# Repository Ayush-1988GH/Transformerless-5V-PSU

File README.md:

# Transformerless-5V-PSU
A compact transformerless AC-to-DC power supply designed using a capacitive dropper, bridge rectifier, zener protection, and LM7805 voltage regulator.  This project was built to understand low-power offline power supply design and mains-side electronics.

## Features
- 230V AC input
- Capacitive current limiting
- Full-wave bridge rectification
- Ripple filtering
- Zener overvoltage protection
- Regulated 5V DC output
- LED power indication

| Component    | Purpose            |
| ------------ | ------------------ |
| X2 Capacitor | Current limiting   |
| 1N4007       | Rectification      |
| LM7805       | 5V regulation      |
| Zener Diode  | Voltage protection |

⚠ WARNING:
This circuit is non-isolated from AC mains.
Do NOT touch while powered.
Do NOT connect directly to a computer USB port.
Only for educational and experimental purposes.

## What I Learned
- Basics of capacitive dropper supplies
- AC to DC rectification
- PCB design considerations for mains voltage
- Filtering and voltage regulation
- Safety considerations in non-isolated supplies

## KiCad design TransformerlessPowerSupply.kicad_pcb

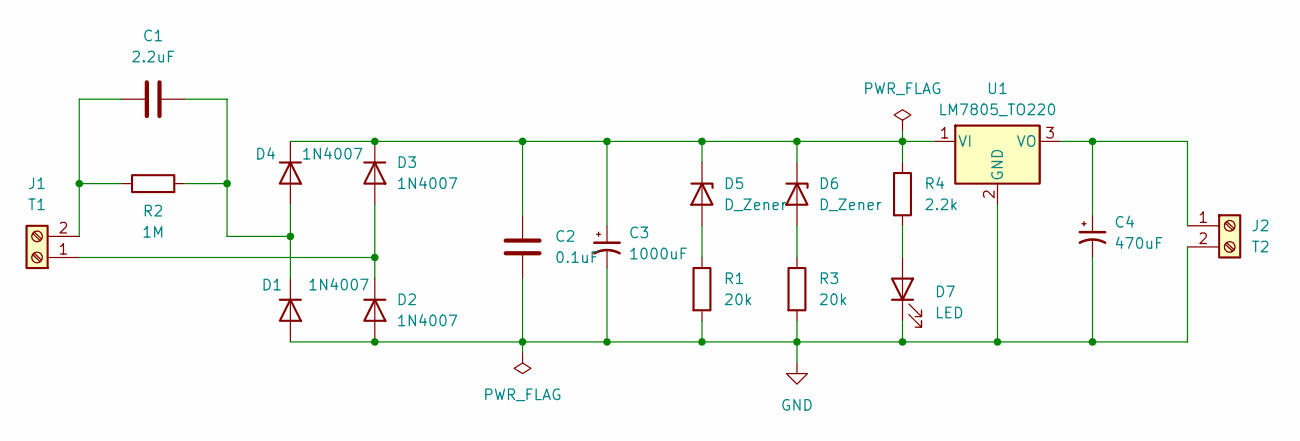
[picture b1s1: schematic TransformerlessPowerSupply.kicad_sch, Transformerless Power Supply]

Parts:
C1: 2.2uF; C_Rect_L18.0mm_W6.0mm_P15.00mm_FKS3_FKP3
C2: 0.1uF; C_Disc_D10.0mm_W2.5mm_P5.00mm
C3: 1000uF; CP_Axial_L10.0mm_D4.5mm_P15.00mm_Horizontal
C4: 470uF; CP_Elec_3x5.4
D1, D2, D3, D4: 1N4007; D_DO-41_SOD81_P10.16mm_Horizontal
D5, D6: D_Zener; D_DO-34_SOD68_P7.62mm_Horizontal
D7: LED; LED_1206_3216Metric
J1: T1; TerminalBlock_Phoenix_PT-1,5-2-5.0-H_1x02_P5.00mm_Horizontal
J2: T2; TerminalBlock_Phoenix_MKDS-1-2-3.81_1x02_P3.81mm_Horizontal
R1, R3: 20k; R_Axial_DIN0204_L3.6mm_D1.6mm_P7.62mm_Horizontal
R2: 1M; R_Axial_DIN0207_L6.3mm_D2.5mm_P15.24mm_Horizontal
R4: 2.2k; R_1206_3216Metric
U1: LM7805_TO220; TO-220-3_Vertical

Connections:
GND: C2.2, C3.2, C4.2, D1.2 (A), D2.2 (A), D7.1 (K), J2.2, R1.2, R3.2, U1.2 (GND)
unnamed: C1.2, D1.1 (K), D4.2 (A), R2.2
unnamed: D2.1 (K), D3.2 (A), J1.1
unnamed: C2.1, C3.1, D3.1 (K), D4.1 (K), D5.1 (K), D6.1 (K), R4.1, U1.1 (VI)
unnamed: D5.2 (A), R1.1
unnamed: D6.2 (A), R3.1
unnamed: D7.2 (A), R4.2
unnamed: C1.1, J1.2, R2.1
unnamed: C4.1, J2.1, U1.3 (VO)

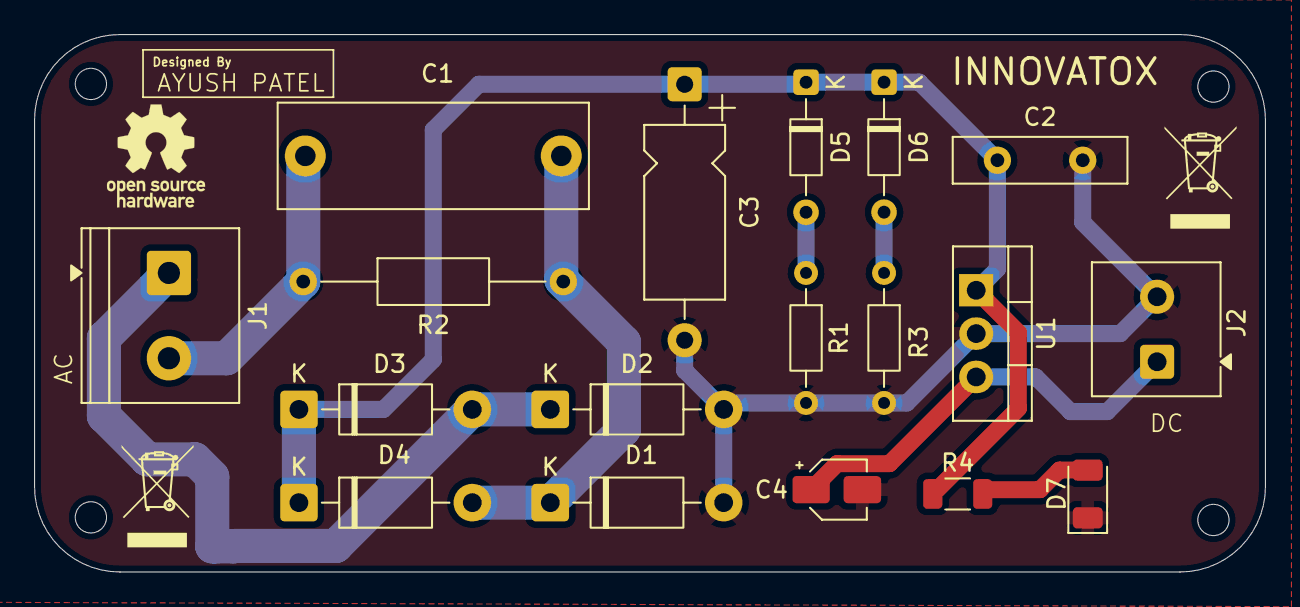
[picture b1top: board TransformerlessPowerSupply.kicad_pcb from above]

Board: 2 copper layers, 72.1 x 31.5 mm, 18 parts (0 on the bottom side), 9 nets.

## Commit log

2026-05-20 Working Principle
2026-05-20 Schematic
    Circuit Diagram
2026-05-20 Schematic Design
    Circuit Diagram
2026-05-20 PCB Layout
2026-05-20 3D View of PCB
2026-05-20 PCB Routing
    Forward layer and backward layer copper path routing
